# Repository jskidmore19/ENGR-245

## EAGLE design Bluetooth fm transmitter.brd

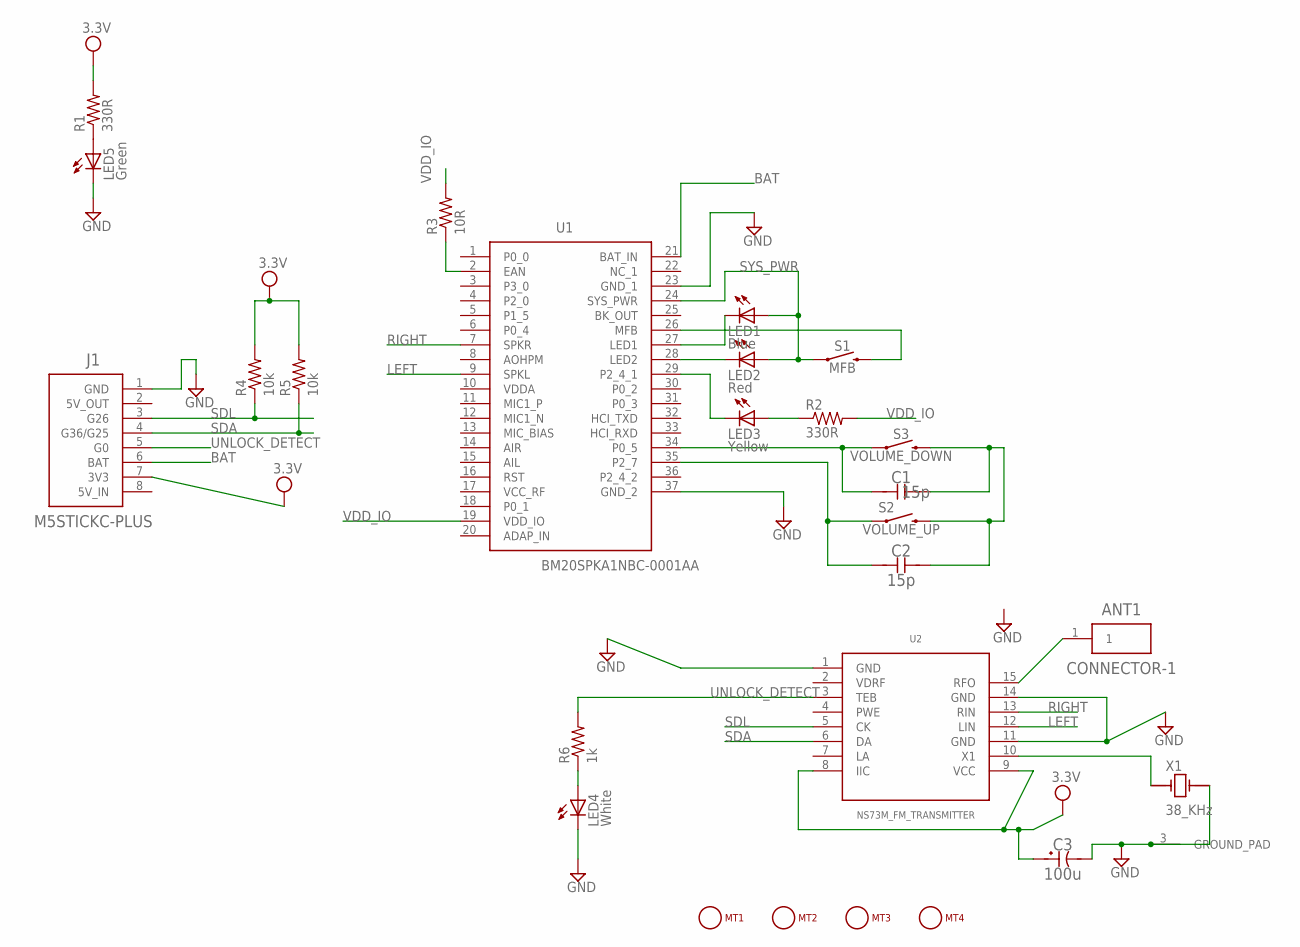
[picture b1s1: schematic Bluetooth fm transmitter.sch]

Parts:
ANT1: CONNECTOR-1; ESQ-101-XX-X-S
C1, C2: 15p; CAPC1608X90L30N
C3: 100u; CAPACITOR_TH_8MM_3.5MM_0.6MM
J1: M5STICKC-PLUS
LED1: Blue; LED5MM
LED2: Red; LED5MM
LED3: Yellow; LED5MM
LED4: White; LED5MM
LED5: Green; LED5MM
MT1, MT2, MT3, MT4: MOUNTING_HOLE-125_250_ROUND; MT_125_250
R1, R2: 330R; V234/12
R3: 10R; V234/12
R4, R5: 10k; V234/12
R6: 1k; V234/12
S1: MFB; TACTILE_SWITCH_PTH_6.0MM
S2: VOLUME_UP; TACTILE_SWITCH_PTH_6.0MM
S3: VOLUME_DOWN; TACTILE_SWITCH_PTH_6.0MM
U1: BM20SPKA1NBC-0001AA; BM20SPKA1NBC0001AA
U2: NS73M_FM_TRANSMITTER; NS73M
X1: 38_KHz; XTAL-WITH-GROUND-PAD

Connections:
3.3V: C3.POSITIVE (1), J1.7 (3V3), R1.2, R4.2, R5.2, U2.8 (IIC), U2.9 (VCC)
BAT: J1.6 (BAT), U1.21 (BAT_IN)
GND: C3.NEGATIVE (2), J1.1 (GND), LED4.K (C), LED5.K (C), U1.23 (GND_1), U1.37 (GND_2), U2.1 (GND), U2.11 (GND), U2.14 (GND), X1.2, X1.3 (GROUND_PAD)
LEFT: U1.9 (SPKL), U2.12 (LIN)
unnamed: ANT1.1, U2.15 (RFO)
unnamed: LED5.A, R1.1
unnamed: R3.1, U1.2 (EAN)
unnamed: S1.3 (2), U1.26 (MFB)
unnamed: LED1.K (C), U1.27 (LED1)
unnamed: LED2.K (C), U1.28 (LED2)
unnamed: LED3.K (C), U1.29 (P2_4_1)
unnamed: LED3.A, R2.1
unnamed: LED4.A, R6.1
unnamed: U2.10 (X1), X1.1
unnamed: C2.1, S2.1, U1.35 (P2_7)
unnamed: C1.1, S3.1, U1.34 (P0_5)
unnamed: C1.2, C2.2, S2.3 (2), S3.3 (2)
RIGHT: U1.7 (SPKR), U2.13 (RIN)
SDA: J1.4 (G36/G25), R5.1, U2.6 (DA)
SDL: J1.3 (G26), R4.1, U2.5 (CK)
SYS_PWR: LED1.A, LED2.A, S1.1, U1.24 (SYS_PWR)
UNLOCK_DETECT: J1.5 (G0), R6.2, U2.3 (TEB)
VDD_IO: R2.2, R3.2, U1.19 (VDD_IO)

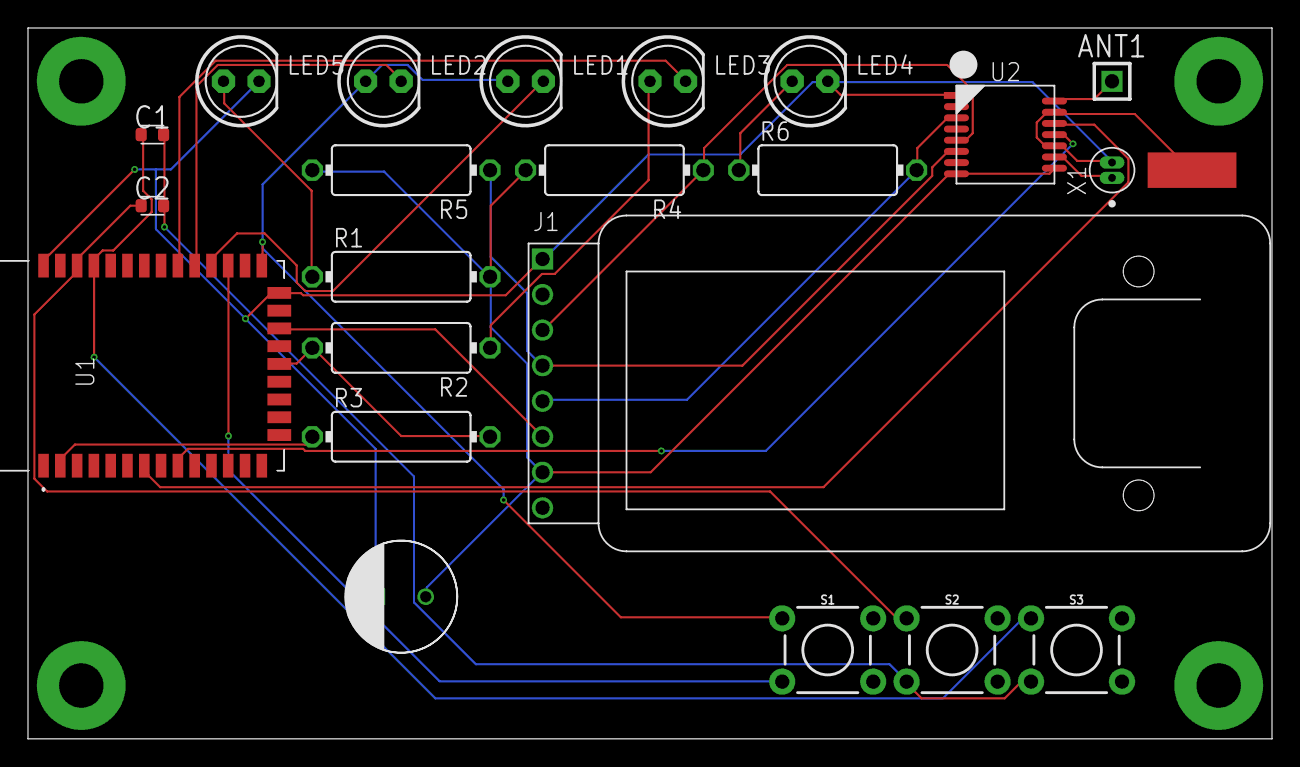
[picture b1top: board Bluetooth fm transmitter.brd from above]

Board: 2 copper layers, 88.9 x 50.8 mm, 26 parts (0 on the bottom side), 23 nets.

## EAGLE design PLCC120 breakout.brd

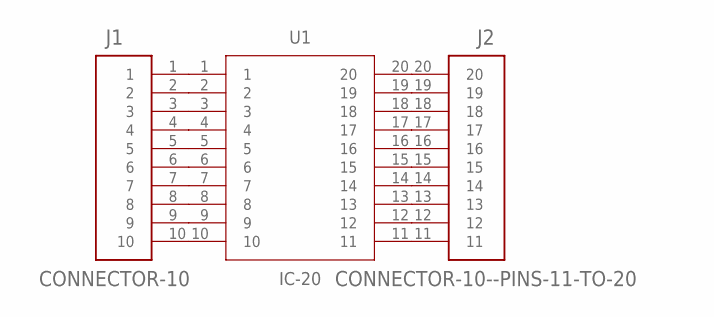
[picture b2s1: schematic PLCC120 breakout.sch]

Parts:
J1: CONNECTOR-10; ESQ-110-XX-XX-S
J2: CONNECTOR-10--PINS-11-TO-20; ESQ-110-XX-XX-S--ROUND-PIN-1
U1: IC-20; PLCC127P990X990X457-20N

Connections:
unnamed: J1.4, U1.4
unnamed: J1.1, U1.1
unnamed: J1.5, U1.5
unnamed: J1.2, U1.2
unnamed: J1.6, U1.6
unnamed: J1.3, U1.3
unnamed: J1.7, U1.7
unnamed: J1.8, U1.8
unnamed: J1.9, U1.9
unnamed: J1.10, U1.10
unnamed: J2.14, U1.14
unnamed: J2.11, U1.11
unnamed: J2.15, U1.15
unnamed: J2.12, U1.12
unnamed: J2.16, U1.16
unnamed: J2.13, U1.13
unnamed: J2.17, U1.17
unnamed: J2.18, U1.18
unnamed: J2.19, U1.19
unnamed: J2.20, U1.20

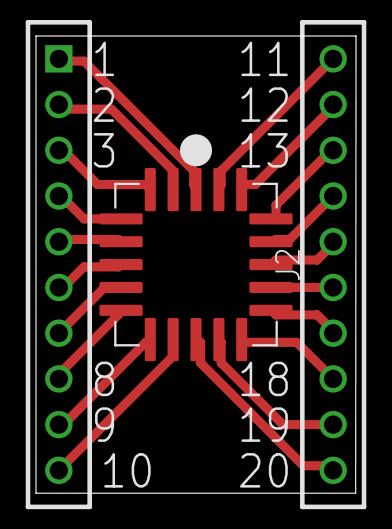
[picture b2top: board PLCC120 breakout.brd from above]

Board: 2 copper layers, 17.8 x 25.4 mm, 3 parts (0 on the bottom side), 20 nets.
